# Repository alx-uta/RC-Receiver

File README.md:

# RC-Receiver
This is a custom RC Receiver that's using ESP32 and Semtech SX1280

Authors:
- Marian Uta

# Project Status - WIP
- [https://microknot.dev/rc-receiver-project-status/](https://microknot.dev/rc-receiver-project-status/)

---
Links:
- [Discord](https://discord.gg/eHyz2aJ6)

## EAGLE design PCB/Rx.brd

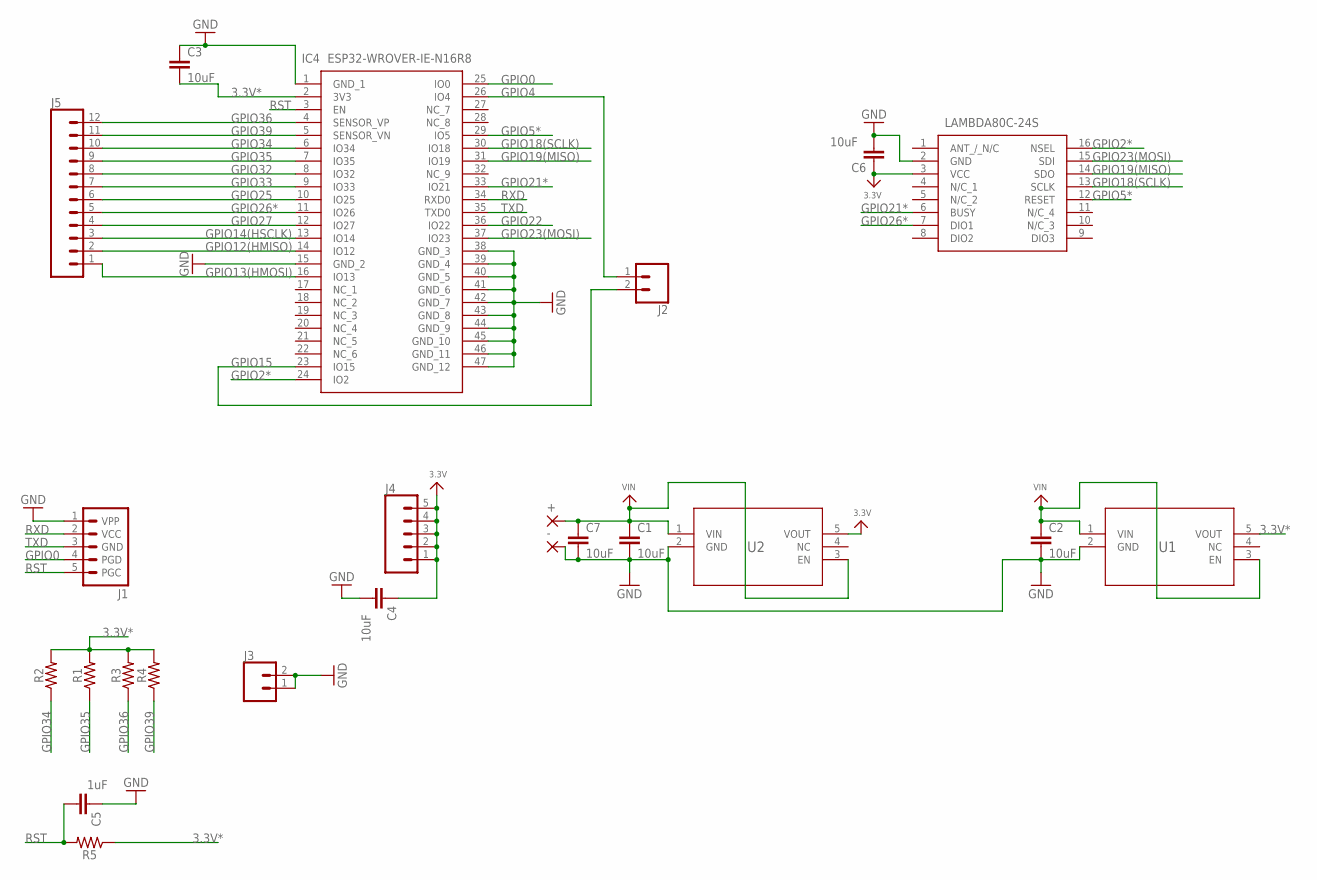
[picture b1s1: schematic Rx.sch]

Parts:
+: 2,15/1,0
-: 2,15/1,0
C1, C2, C3, C4, C6, C7: 10uF; 0805
C5: 1uF; 0805
IC1: LAMBDA80C-24S; LAMBDA80C24S
IC4: ESP32-WROVER-IE-N16R8; ESP32WROVERIEN16R8
J1: PIC_ICSP_MINI_5_PIN
J2, J3: CONN_021X02_NO_SILK; 1X02_NO_SILK
J4: CONN_05NO_SILK; 1X05_NO_SILK
J5: CONN_12NO_SILK; 1X12_NO_SILK
R1, R2, R3, R4, R5: 0; 0603
U1, U2: AP2112K-3.3TRG1SOT_RG1_DIO-L; SOT_RG1_DIO-L

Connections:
3.3V: C4.1, C6.1, IC1.3 (VCC), J4.1, J4.2, J4.3, J4.4, J4.5, U2.5 (VOUT)
3.3V*: C3.2, IC4.2 (3V3), R1.2, R2.2, R3.2, R4.2, R5.1, U1.5 (VOUT)
GND: -.1, C1.2, C2.2, C3.1, C4.2, C5.1, C6.2, C7.2, IC1.2 (GND), IC4.1 (GND_1), IC4.15 (GND_2), IC4.38 (GND_3), IC4.39 (GND_4), IC4.40 (GND_5), IC4.41 (GND_6), IC4.42 (GND_7), IC4.43 (GND_8), IC4.44 (GND_9), IC4.45 (GND_10), IC4.46 (GND_11), IC4.47 (GND_12), J1.1 (VPP), J3.1, J3.2, U1.2 (GND), U2.2 (GND)
GPIO0: IC4.25 (IO0), J1.4 (PGD)
GPIO2*: IC1.16 (NSEL), IC4.24 (IO2)
GPIO4: IC4.26 (IO4), J2.1
GPIO5*: IC1.12 (RESET), IC4.29 (IO5)
GPIO12(HMISO): IC4.14 (IO12), J5.2
GPIO13(HMOSI): IC4.16 (IO13), J5.1
GPIO14(HSCLK): IC4.13 (IO14), J5.3
GPIO15: IC4.23 (IO15), J2.2
GPIO18(SCLK): IC1.13 (SCLK), IC4.30 (IO18)
GPIO19(MISO): IC1.14 (SDO), IC4.31 (IO19)
GPIO21*: IC1.6 (BUSY), IC4.33 (IO21)
GPIO22: IC4.36 (IO22)
GPIO23(MOSI): IC1.15 (SDI), IC4.37 (IO23)
GPIO25: IC4.10 (IO25), J5.6
GPIO26*: IC1.7 (DIO1), IC4.11 (IO26), J5.5
GPIO27: IC4.12 (IO27), J5.4
GPIO32: IC4.8 (IO32), J5.8
GPIO33: IC4.9 (IO33), J5.7
GPIO34: IC4.6 (IO34), J5.10, R2.1
GPIO35: IC4.7 (IO35), J5.9, R1.1
GPIO36: IC4.4 (SENSOR_VP), J5.12, R3.1
GPIO39: IC4.5 (SENSOR_VN), J5.11, R4.1
RST: C5.2, IC4.3 (EN), J1.5 (PGC), R5.2
RXD: IC4.34 (RXD0), J1.2 (VCC)
TXD: IC4.35 (TXD0), J1.3 (GND)
VIN: +.1, C1.1, C2.1, C7.1, U1.1 (VIN), U1.3 (EN), U2.1 (VIN), U2.3 (EN)

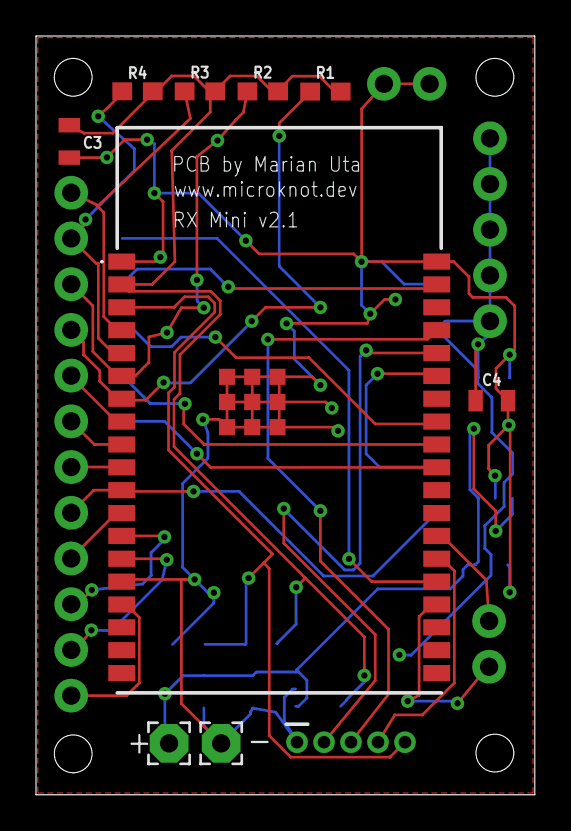
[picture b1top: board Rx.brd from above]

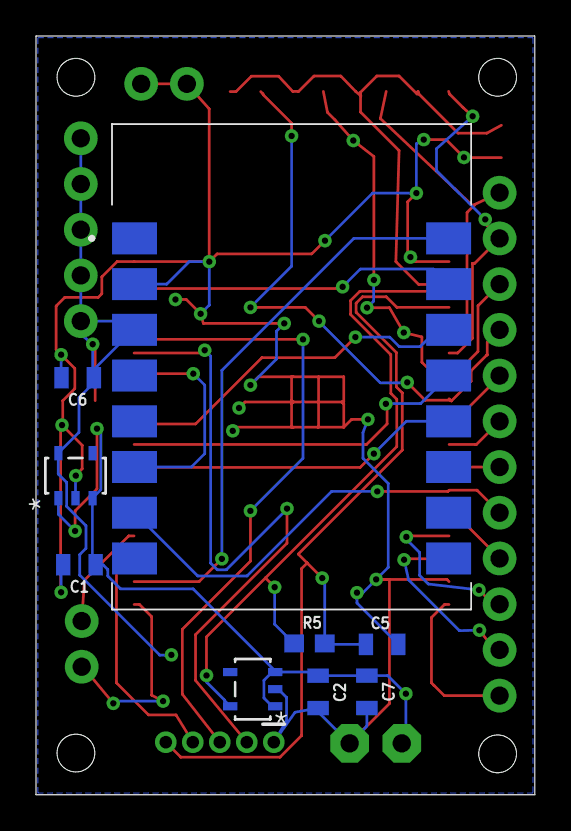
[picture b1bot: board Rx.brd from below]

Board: 2 copper layers, 27.7 x 42.2 mm, 23 parts (9 on the bottom side), 28 nets.

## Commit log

2023-11-12 RC - Receiver
2024-01-06 Code Improvements
    - added binding key
    - new variable to allow debug on all channels
2025-04-07 RC Receiver - Car
2025-04-12 FLRC
2025-04-12 FLRC & build ignore
2025-04-17 rover, example
2025-04-17 FLRC Update

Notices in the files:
parts and their libraries:
SparkFun-Capacitors: Licensing: Creative Commons ShareAlike 4.0 International - https://creativecommons.org/licenses/by-sa/4.0
COPYRIGHT: Copyright (C) 2023 Ultra Librarian. All rights reserved.
